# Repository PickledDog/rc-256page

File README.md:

# rc-256page
 128K+128K fully pageable RAM/ROM card for RC2014

## Overview
This RC2014-compatible board provides RAM and flash ROM, software-pageable in 32k pages. 4 ROM and 4 RAM pages may be paged into both the lower and upper 32k of Z80 memory.

## Memory details
For ROM, a SST39SF010 128k x 8 flash chip is used. It can be programmed in-place using Will Sowerbutts' FLASH4 utility (included with RomWBW). For RAM, an AS6C1008 128k x 8 SRAM is used, providing 128K of addressable memory. Both are divided into 32k pages, and are presented to the system via 2 32k address blocks (so 2 pages selectable from 8 total).

## Paging
Upon reset, ROM page 0 is mapped to both the lower **and** upper 32k (initialization code in page 0 *must* select a RAM page for normal operation). A single config register is used to set **both** currently mapped pages, presented as an I/O device at 0x78 (the address used by most "large" Z80 memory systems). The low nibble of this configures the lower page, and the high nibble the higher page. For each nibble, the high bit selects the chip (0 for ROM, 1 for RAM).

## Firmware
This board can be used as an affordable way to add [RomWBW](https://github.com/wwarthen/RomWBW) support to an RC2014 (see below). It is also presented as a programming challenge for adventurous RC2014 builders, who want an inexpensive way to add fully software-pageable memory to their computers. Beyond RomWBW, *there are currently no standard ROM images for this board* (that is, no BASIC ROM etc). None of the standard RC2014 ROM images can be used as-is. Building a ROM image (or modifying an existing one) is left up to the user.

### RomWBW
For RomWBW, a new memory mapper needs to be added. A patch file to do this can be found in the [firmware](/firmware) directory (along with an example image).

## Part selection
Bill Of Materials and part references are below. I recommend using gold-plated header for the bus connection - I use these ones from [Pololu](https://www.pololu.com/product/967) or [Sparkfun](https://www.sparkfun.com/products/553). A nice detail of these, is that they sit at the same height as double-row header in a backplane.

The specified parts are just the ones I used, and can be substituted as needed - Mouser links provided for convenience and reference.

| Reference | Value | Qty | Mouser link |
| --------- | ----- | --- | ----------- |
| C1-C5 | 100nF ceramic | 5 | [KEMET C315C104M5U5TA](https://www.mouser.com/ProductDetail/C315C104M5U5TA7303) |
| J1 | 1x40 right-angle header | 1 | [Wurth 61304011021](https://www.mouser.com/ProductDetail/61304011021) |
| R1 | 4k7Ω resistor | 1 | [Yageo CFR-25JT-52-4K7](https://www.mouser.com/ProductDetail/CFR-25JT-52-4K7) |
| U1 | SST39SF010 NOR flash | 1 | [Microchip SST39SF010A-70-4C-PHE](https://www.mouser.com/ProductDetail/SST39SF010A-70-4C-PHE) |
| U2 | AS6C1008 SRAM | 1 | [Alliance AS6C1008-55PCN](https://www.mouser.com/ProductDetail/AS6C1008-55PCN) |
| | sockets | 2 | [Amphenol DILB32P-223TLF](https://www.mouser.com/ProductDetail/DILB32P-223TLF) |
| U3 | 74HCT138 | 1 | [TI SN74HCT138N](https://www.mouser.com/ProductDetail/SN74HCT138N) |
| U4 | 74HCT174 | 1 | [TI CD74HCT174E](https://www.mouser.com/ProductDetail/CD74HCT174E) |
| U5 | 74HCT257 | 1 | [TI SN74HCT257N](https://www.mouser.com/ProductDetail/SN74HCT257N) |

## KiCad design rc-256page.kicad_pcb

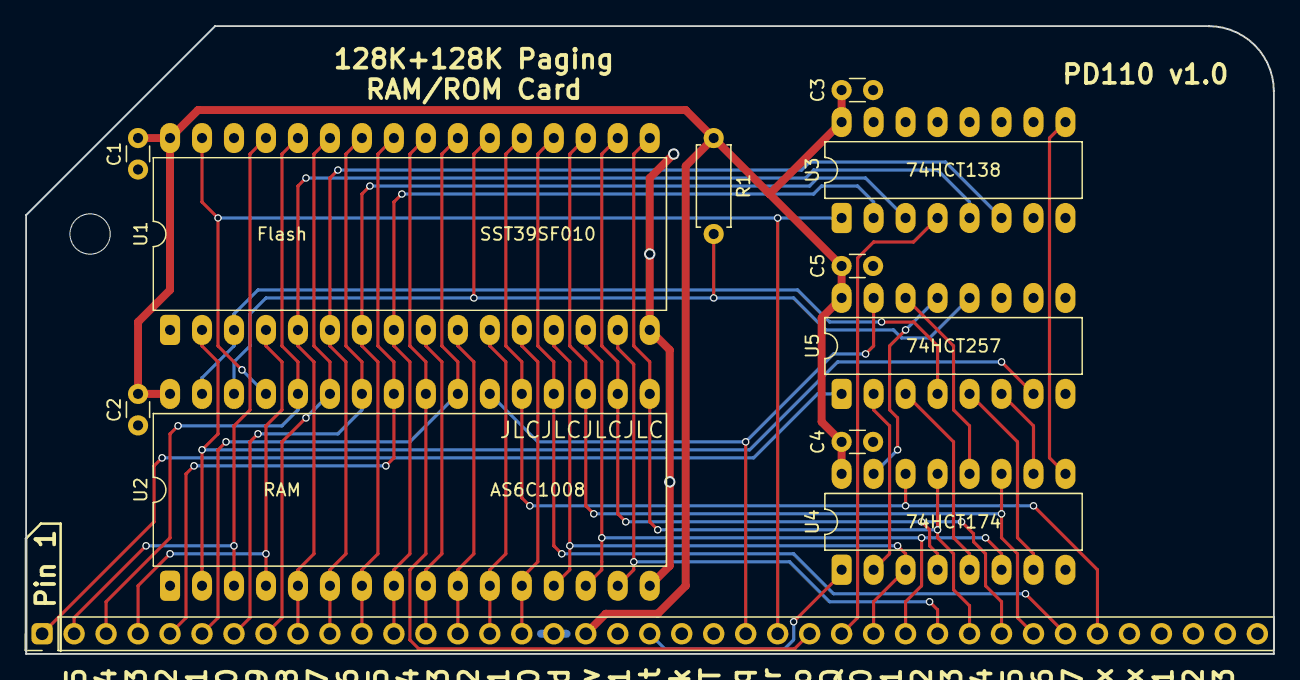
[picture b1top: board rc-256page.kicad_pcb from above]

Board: 2 copper layers, 99.1 x 49.9 mm, 12 parts (0 on the bottom side), 41 nets.

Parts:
C1, C2, C3, C4, C5: 0.1uF; C_Disc_D3.0mm_W1.6mm_P2.50mm
J1: RC2014; PinHeader_1x39_P2.54mm_Vertical
R1: 4k7; R_Axial_DIN0207_L6.3mm_D2.5mm_P7.62mm_Horizontal
U1: SST39SF010; DIP-32_W15.24mm_LongPads
U2: AS6C1008; DIP-32_W15.24mm_LongPads
U3: 74HCT138; DIP-16_W7.62mm_LongPads
U4: 74HCT174; DIP-16_W7.62mm_LongPads
U5: 74HCT257; DIP-16_W7.62mm_LongPads

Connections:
+5V: C1.1, C2.1, C3.2, C4.2, C5.2, J1.18, R1.1, U1.32, U2.32, U3.16, U4.16, U5.16
/A15A: U4.2, U5.2
/A15B: U4.5, U5.3
/A16A: U4.7, U5.5
/A16B: U4.10, U5.6
/~CFG_CS: U3.9, U4.9
/~ROMA: U4.12, U5.14
/~ROMB: U4.15, U5.13
A0: J1.16, U1.12, U2.12
A1: J1.15, U1.11, U2.11
A2: J1.14, U1.10, U2.10
A3: J1.13, U1.9, U2.9
A4: J1.12, U1.8, U2.8, U3.2
A5: J1.11, U1.7, U2.7, U3.3
A6: J1.10, U1.6, U2.6, U3.6
A7: J1.9, U1.5, U2.5, U3.5
A8: J1.8, U1.27, U2.27
A9: J1.7, U1.26, U2.26
A10: J1.6, U1.23, U2.23
A11: J1.5, U1.25, U2.25
A12: J1.4, U1.4, U2.4
A13: J1.3, U1.28, U2.28
A14: J1.2, U1.29, U2.3
A15: J1.1, U5.1
D0: J1.27, U1.13, U2.13, U4.3
D1: J1.28, U1.14, U2.14, U4.6
D2: J1.29, U1.15, U2.15
D3: J1.30, U1.17, U2.17, U4.13
D4: J1.31, U1.18, U2.18, U4.4
D5: J1.32, U1.19, U2.19, U4.11
D6: J1.33, U1.20, U2.20
D7: J1.34, U1.21, U2.21, U4.14
GND: C1.2, C2.2, C3.1, C4.1, C5.1, J1.17, U1.16, U2.16, U3.8, U4.8, U5.8, U5.10, U5.11
MEM_A15: U1.3, U2.31, U5.4
MEM_A16: U1.2, U2.2, U5.7
~IOREQ: J1.26, U3.4
~MREQ: J1.23, U2.22, U5.15
~RD: J1.25, U1.24, U2.24
~RESET: J1.20, U4.1
~ROM_CS: R1.2, U1.22, U2.30, U5.12
~WR: J1.24, U1.31, U2.29, U3.1

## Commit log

2021-03-27 Initial commit of rc-256page/PD110
2021-03-28 Add README and picture
2021-04-05 Minor layout tweaks
2021-04-20 Add RomWBW patch and binary
2021-07-06 Fix missing BOM entry
